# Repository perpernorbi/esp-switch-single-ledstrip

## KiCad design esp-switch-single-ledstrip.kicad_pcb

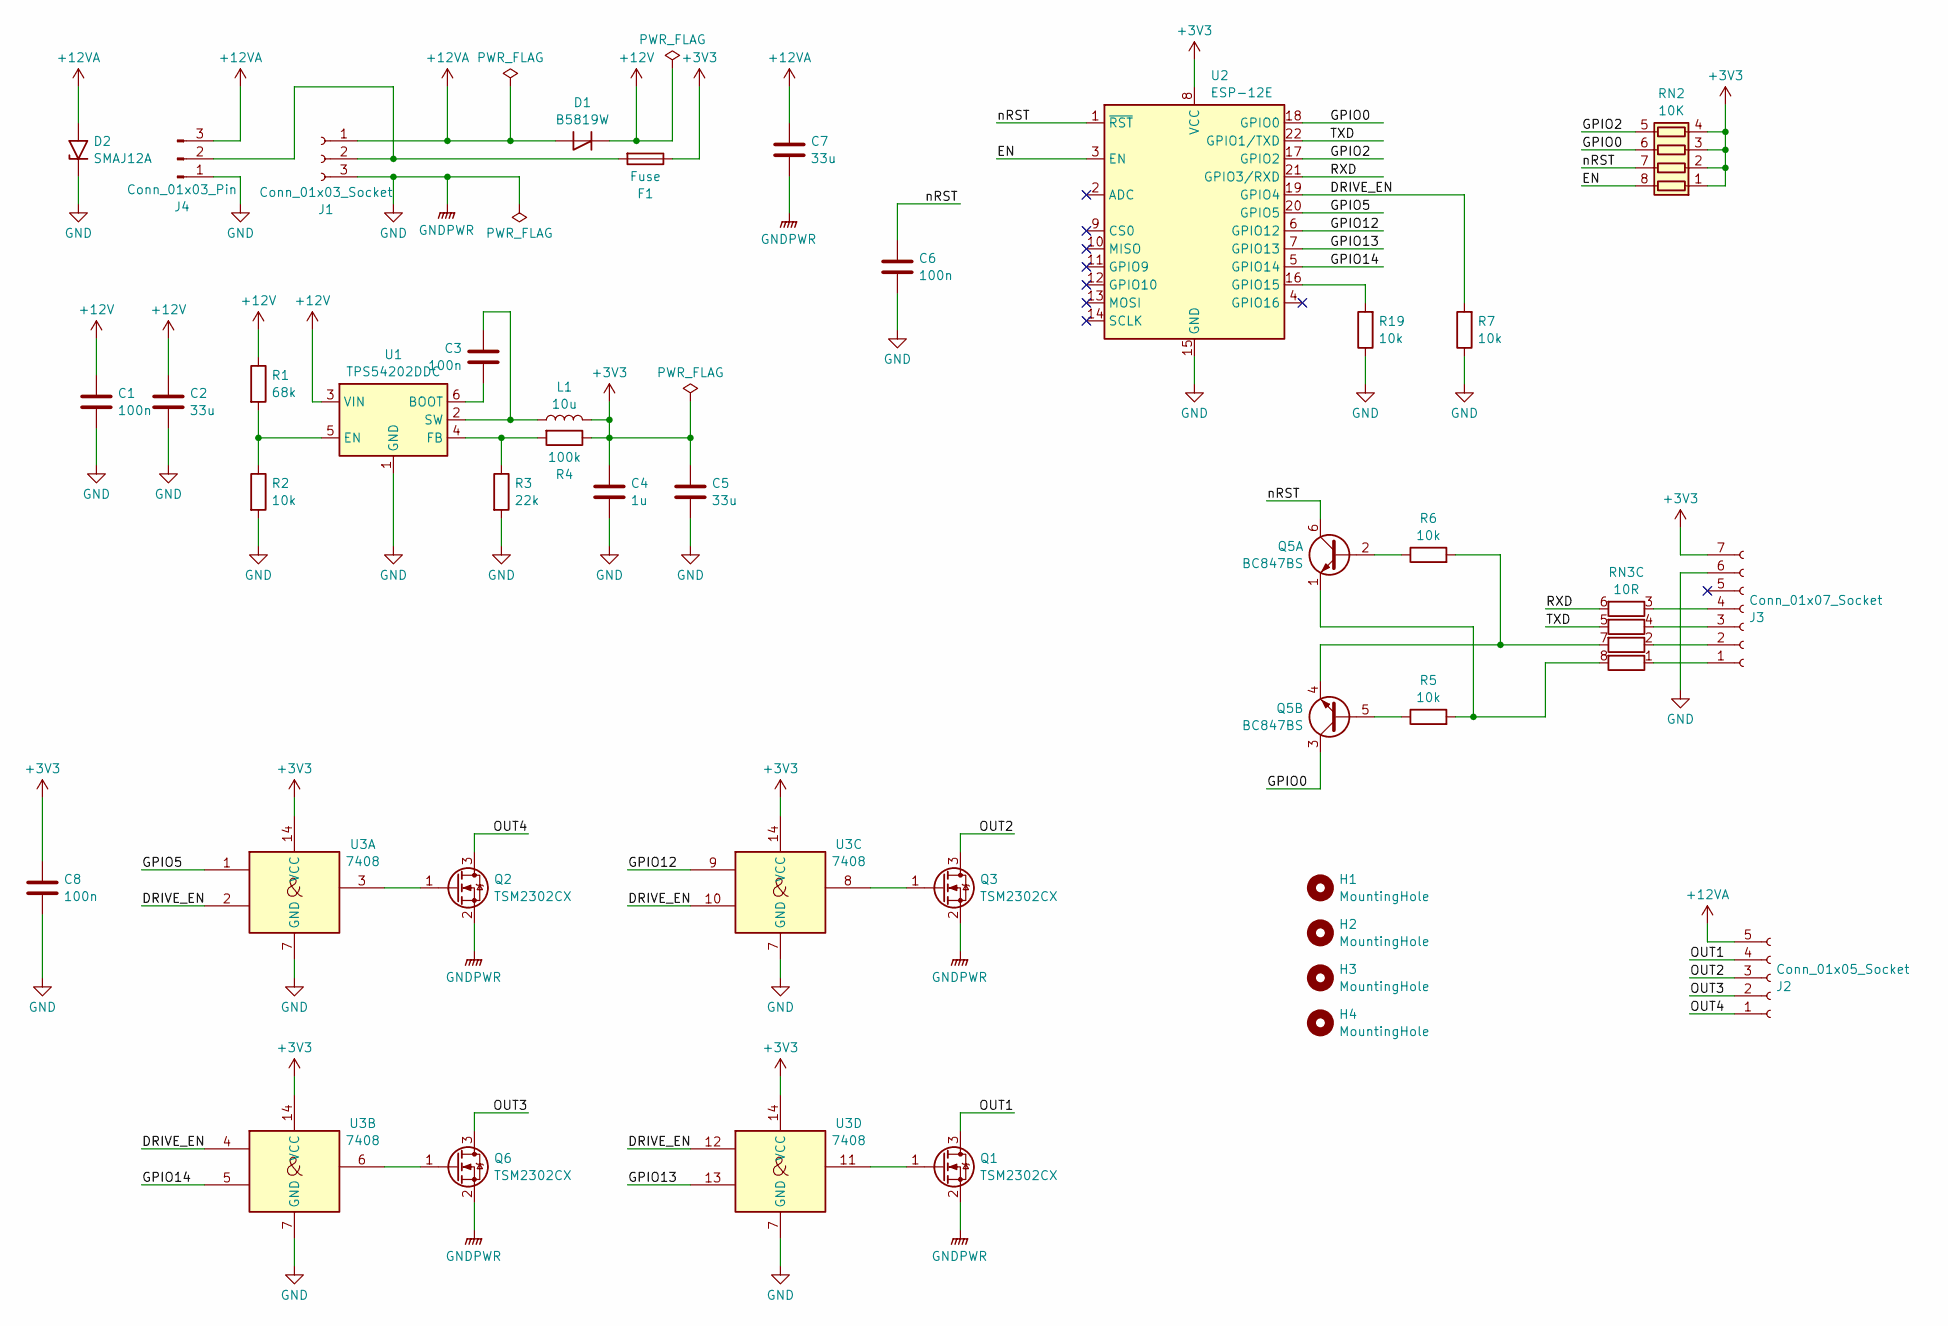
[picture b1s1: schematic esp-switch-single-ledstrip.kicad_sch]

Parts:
C1, C3, C6, C8: 100n; C_0805_2012Metric_Pad1.18x1.45mm_HandSolder
C2, C5, C7: 33u; C_1812_4532Metric_Pad1.57x3.40mm_HandSolder
C4: 1u; C_0805_2012Metric_Pad1.18x1.45mm_HandSolder
D1: B5819W; D_SOD-123
D2: SMAJ12A; D_SMA
F1: Fuse; Fuse_1812_4532Metric_Pad1.30x3.40mm_HandSolder
H1, H2, H3, H4: MountingHole; MountingHole_3.2mm_M3_ISO7380
J1: Conn_01x03_Socket; PinSocket_1x03_P2.54mm_Horizontal
J2: Conn_01x05_Socket; PinSocket_1x05_P2.54mm_Horizontal
J3: Conn_01x07_Socket; PinSocket_1x07_P2.54mm_Horizontal
J4: Conn_01x03_Pin; PinHeader_1x03_P2.54mm_Horizontal
L1: 10u; L_6.5x6.5_H4.6
Q1, Q2, Q3, Q6: TSM2302CX; SOT-23
Q5: BC847BS; SOT-363_SC-70-6
R1: 68k; R_0805_2012Metric_Pad1.20x1.40mm_HandSolder
R2, R5, R6, R7, R19: 10k; R_0805_2012Metric_Pad1.20x1.40mm_HandSolder
R3: 22k; R_0805_2012Metric_Pad1.20x1.40mm_HandSolder
R4: 100k; R_0805_2012Metric_Pad1.20x1.40mm_HandSolder
RN2: 10K; R_Array_Convex_4x0612
RN3: 10R; R_Array_Convex_4x0612
U1: TPS54202DDC; SOT-23-6
U2: ESP-12E
U3: 7408; TSSOP-14_4.4x5mm_P0.65mm

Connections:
+3V3: C4.1, C5.1, C8.1, F1.1, J3.7, L1.2, R4.1, RN2.1 (R1.1), RN2.2 (R2.1), RN2.3 (R3.1), RN2.4 (R4.1), U2.8 (VCC), U3.14 (VCC)
+12V: C1.1, C2.1, D1.1 (K), R1.1, U1.3 (VIN)
+12VA: C7.1, D1.2 (A), D2.2 (A2), J1.1, J2.5, J4.3
/DRIVE_EN: R7.2, U2.19 (GPIO4), U3.2, U3.4, U3.10, U3.12
/EN: RN2.8 (R1.2), U2.3 (EN)
/GPIO0: Q5.3 (C2), RN2.6 (R3.2), U2.18 (GPIO0)
/GPIO2: RN2.5 (R4.2), U2.17 (GPIO2)
/GPIO5: U2.20 (GPIO5), U3.1
/GPIO12: U2.6 (GPIO12), U3.9
/GPIO13: U2.7 (GPIO13), U3.13
/GPIO14: U2.5 (GPIO14), U3.5
/OUT1: J2.4, Q1.3 (D)
/OUT2: J2.3, Q3.3 (D)
/OUT3: J2.2, Q6.3 (D)
/OUT4: J2.1, Q2.3 (D)
/RXD: RN3.6 (R3.2), U2.21 (GPIO3/RXD)
/TXD: RN3.5 (R4.2), U2.22 (GPIO1/TXD)
/nRST: C6.1, Q5.6 (C1), RN2.7 (R2.2), U2.1 (~RST)
GND: C1.2, C2.2, C4.2, C5.2, C6.2, C7.2, C8.2, D2.1 (A1), J1.3, J3.6, J4.1, Q1.2 (S), Q2.2 (S), Q3.2 (S), Q6.2 (S), R2.2, R3.2, R7.1, R19.1, U1.1 (GND), U2.15 (GND), U3.7 (GND)
unnamed: F1.2, J1.2, J4.2
unnamed: J3.1, RN3.1 (R1.1)
unnamed: J3.2, RN3.2 (R2.1)
unnamed: J3.3, RN3.4 (R4.1)
unnamed: J3.4, RN3.3 (R3.1)
unnamed: Q1.1 (G), U3.11
unnamed: Q2.1 (G), U3.3
unnamed: Q3.1 (G), U3.8
unnamed: Q5.2 (B1), R6.1
unnamed: Q5.1 (E1), R5.2, RN3.8 (R1.2)
unnamed: Q5.5 (B2), R5.1
unnamed: Q5.4 (E2), R6.2, RN3.7 (R2.2)
unnamed: Q6.1 (G), U3.6
unnamed: C3.1, U1.6 (BOOT)
unnamed: R1.2, R2.1, U1.5 (EN)
unnamed: R3.1, R4.2, U1.4 (FB)
unnamed: C3.2, L1.1, U1.2 (SW)
unnamed: R19.2, U2.16 (GPIO15)

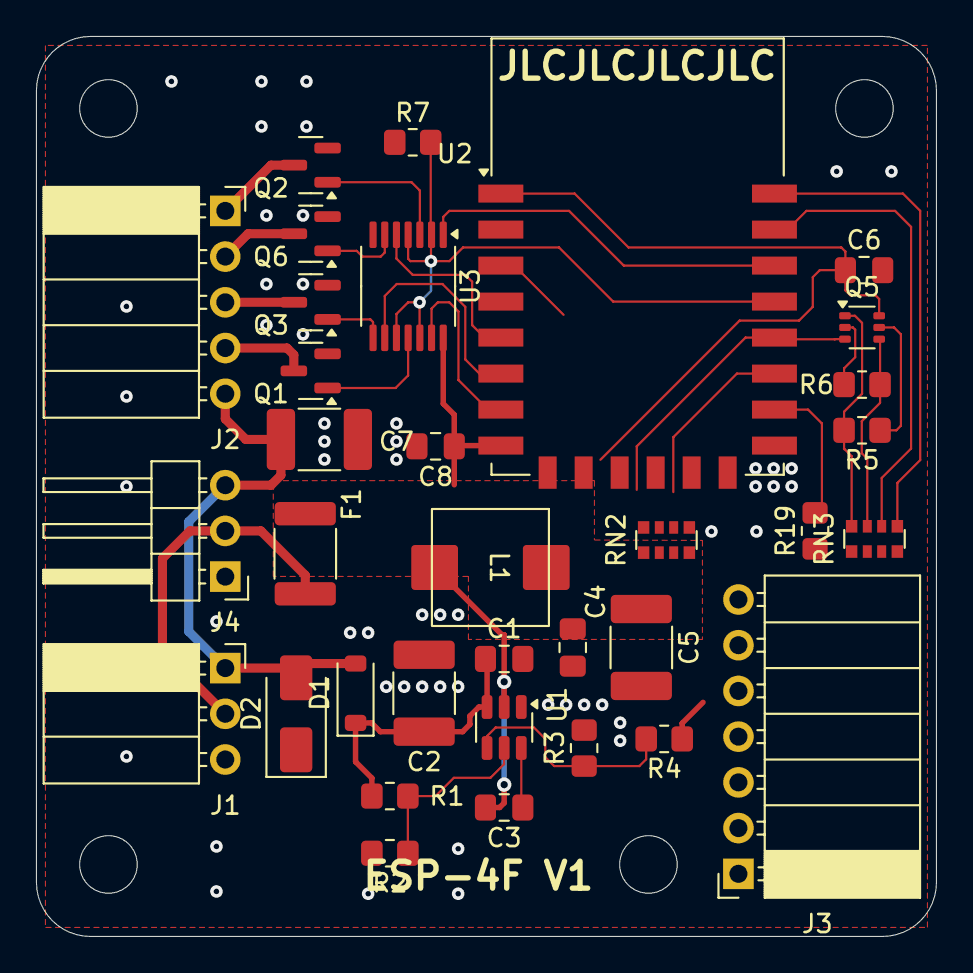
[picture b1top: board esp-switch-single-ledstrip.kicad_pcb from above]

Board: 2 copper layers, 50.0 x 50.0 mm, 38 parts (0 on the bottom side), 37 nets.

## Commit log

2024-12-30 First version
